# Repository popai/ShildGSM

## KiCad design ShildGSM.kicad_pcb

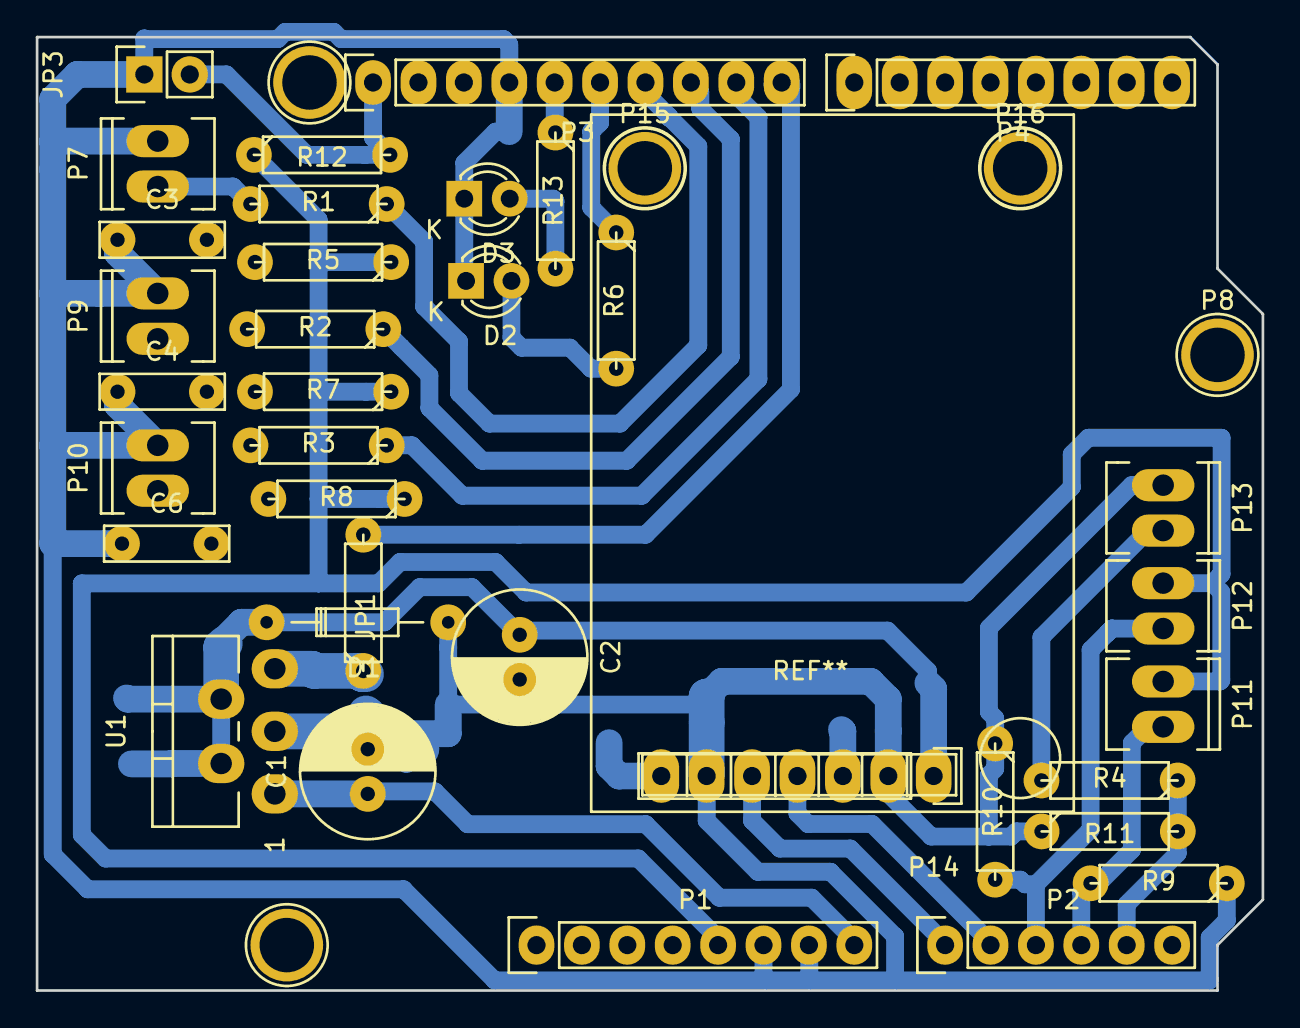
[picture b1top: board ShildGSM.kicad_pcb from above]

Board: 2 copper layers, 68.6 x 53.3 mm, 41 parts (1 on the bottom side), 23 nets.

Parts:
C1, C2: 470uF; C_Radial_D7.5_L11.2_P2.5
C3, C4, C6: 100n; C_Rect_L7_W2_P5
D1: 1N5822; Diode_DO-35_SOD27_Horizontal_RM10
D2: useLED; LED-3MM
D3: errLED; LED-3MM
JP1: JUMPER; R3
JP2: JUMPER; R_0603_HandSoldering
JP3: JUMPER; Pin_Header_Straight_1x02
P1: Power; Socket_Strip_Arduino_1x08
P2: Analog; Socket_Strip_Arduino_1x06
P3: Digital; Socket_Strip_Arduino_1x10
P4: Digital; Socket_Strip_Arduino_1x08
P5, P6, P8, P15, P16: CONN_1; Arduino_1pin
P7, P9, P10, P11, P12, P13: CONN_01X02; Socket_MOLEX-KK-RM2-54mm_Lock_2pin_straight
P14: CONN_01X07; Socket_Strip_Straight_1x07
R1, R2, R3, R6, R13: 1k; R3
R4: 40k; R3
R5, R7, R8, R9, R11, R12: 10k; R3
R10: 10; R3
U1: LM2567T-5; Pentawatt_Neutral_Staggered_Verical_TO220-5-T05D

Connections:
+5V: P1.5, P11.1, P12.1, R5.1, R7.1, R8.1, R12.1
/8: JP1.2, P3.10
/9(**): P3.9, R3.1
/10(**/SS): P3.8, R2.1
/11(**/MOSI): P3.7, R1.1
/12(MISO): P3.6, R6.1
/13(SCK): P3.5, R13.1
/A0: P2.1, P14.5
/A1: P2.2, P14.4
/A2: P2.3, P12.2, R10.2
/A3: P2.4, P11.2, R9.2
/A4(SDA): P2.5, P3.2, R4.1, R11.2
/A5(SCL): JP3.2, P2.6, P3.1, R12.2
/Vin: C1.1, P1.8, U1.1
GND: C1.2, C2.2, C3.1, C4.1, C6.1, D1.2, D2.1, D3.1, JP2.2, JP3.1, P1.6, P1.7, P3.4, P7.2, P9.2, P10.2, P13.1, P14.2, P14.6, R9.1, R10.1, R11.1, U1.3
unnamed: C3.2, P7.1, R1.2, R5.2
unnamed: C4.2, P9.1, R2.2, R7.2
unnamed: C6.2, P10.1, R3.2, R8.2
unnamed: D2.2, R6.2
unnamed: D3.2, R13.2
unnamed: JP1.1, JP2.1, U1.5
unnamed: P13.2, R4.2
VEE: C2.1, D1.1, P14.1, U1.2, U1.4

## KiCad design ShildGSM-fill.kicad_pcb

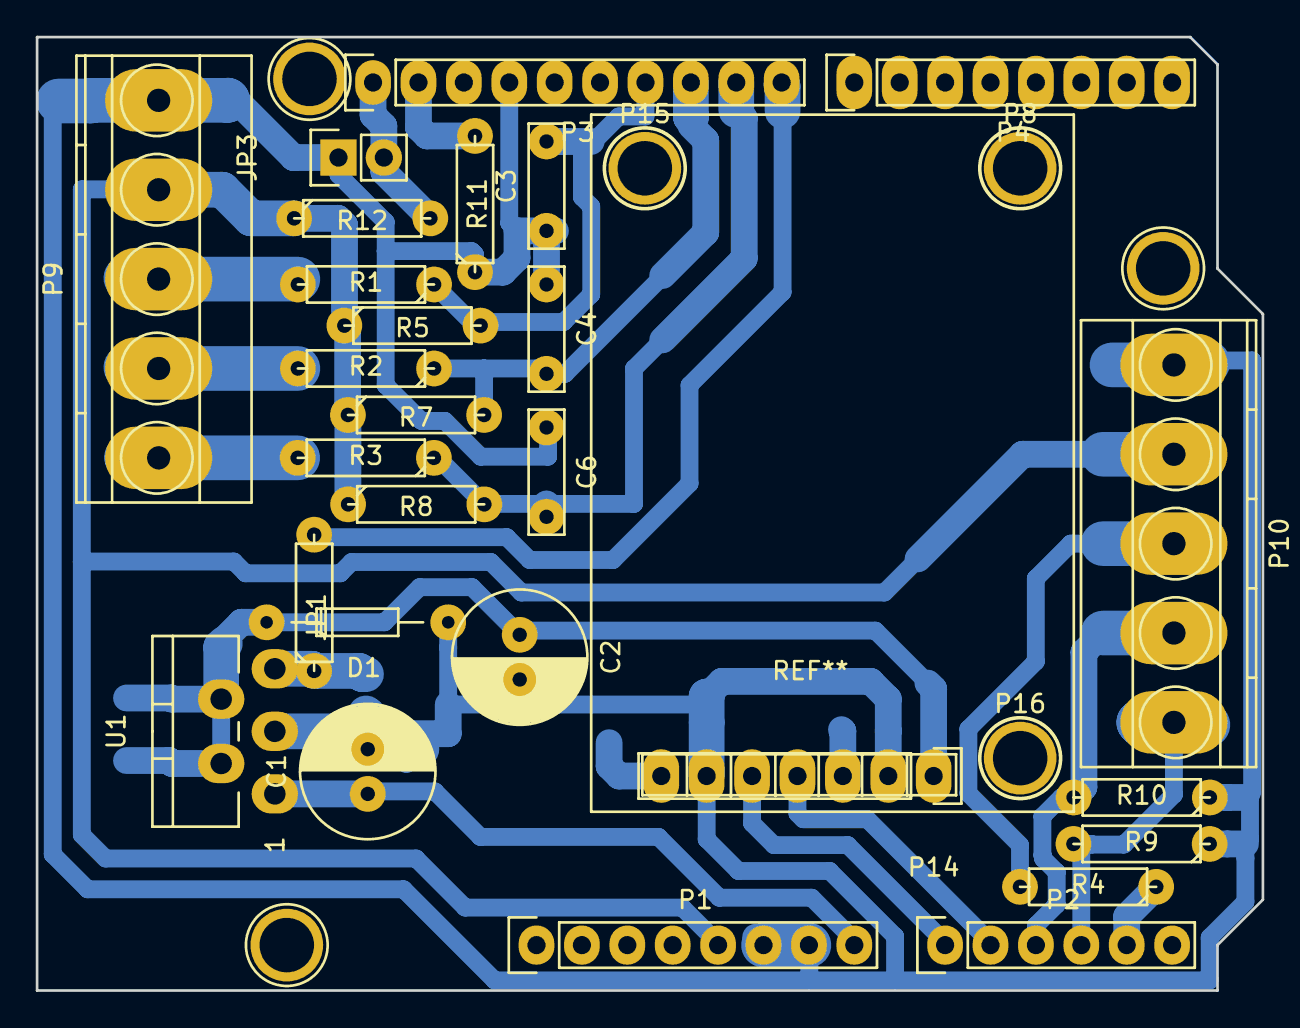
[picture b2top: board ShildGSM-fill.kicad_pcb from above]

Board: 2 copper layers, 68.6 x 53.3 mm, 34 parts (1 on the bottom side), 20 nets.

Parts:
C1, C2: 470uF; C_Radial_D7.5_L11.2_P2.5
C3, C4, C6: 100n; C_Rect_L7_W2_P5
D1: 1N5822; Diode_DO-35_SOD27_Horizontal_RM10
JP1: JUMPER; R3
JP2: JUMPER; R_0603_HandSoldering
JP3: JUMPER; Pin_Header_Straight_1x02
P1: Power; Socket_Strip_Arduino_1x08
P2: Analog; Socket_Strip_Arduino_1x06
P3: Digital; Socket_Strip_Arduino_1x10
P4: Digital; Socket_Strip_Arduino_1x08
P5, P6, P7, P8, P15, P16: CONN_1; Arduino_1pin
P9, P10: CONN_01X05; TerminalBlock_Pheonix_MKDS1.5-5pol
P14: CONN_01X07; Socket_Strip_Straight_1x07
R1, R2, R3: 1k; R3
R4: 40k; R3
R5, R7, R8, R9, R11, R12: 10k; R3
R10: 10; R3
U1: LM2567T-5; Pentawatt_Neutral_Staggered_Verical_TO220-5-T05D

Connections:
+5V: P1.5, P9.2, P10.4, R5.1, R7.1, R8.1, R12.1
/8: JP1.2, P3.10
/9(**): C6.2, P3.9, R3.1, R8.2
/10(**/SS): C4.2, P3.8, R2.1, R7.2
/11(**/MOSI): C3.2, P3.7, R1.1, R5.2
/A0: P2.1, P14.5
/A1: P2.2, P14.4
/A2: P2.3, P10.2, R10.2
/A3: P2.4, P10.1, R9.2
/A4(SDA): P2.5, P3.2, R4.1, R11.2
/A5(SCL): JP3.2, P2.6, P3.1, R12.2
/IOREF: P1.2, P14.3
/Vin: C1.1, P1.8, U1.1
GND: C1.2, C2.2, C3.1, C4.1, C6.1, D1.2, JP2.2, JP3.1, P1.6, P1.7, P3.4, P9.1, P10.5, P14.2, P14.6, R9.1, R10.1, R11.1, U1.3
unnamed: JP1.1, JP2.1, U1.5
unnamed: P9.3, R1.2
unnamed: P9.4, R2.2
unnamed: P9.5, R3.2
unnamed: P10.3, R4.2
VEE: C2.1, D1.1, P14.1, U1.2, U1.4

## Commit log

2016-02-06 :tada: Added .gitattributes & .gitignore files
2016-02-06 Conntroler shild for arduino
    Arduino shild, controler gsm
2016-02-11 corectii
    corectii in schema
2016-02-16 LEDs
    pus led err si led use
2016-02-22 optimizat portare
    Grupat R cu intrarile
